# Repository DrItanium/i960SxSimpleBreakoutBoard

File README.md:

A very simple 4-layer breakout board for an i960Sx PLCC84 microprocessor.

The de-multiplexing hardware is separate in this design for ease of testing.

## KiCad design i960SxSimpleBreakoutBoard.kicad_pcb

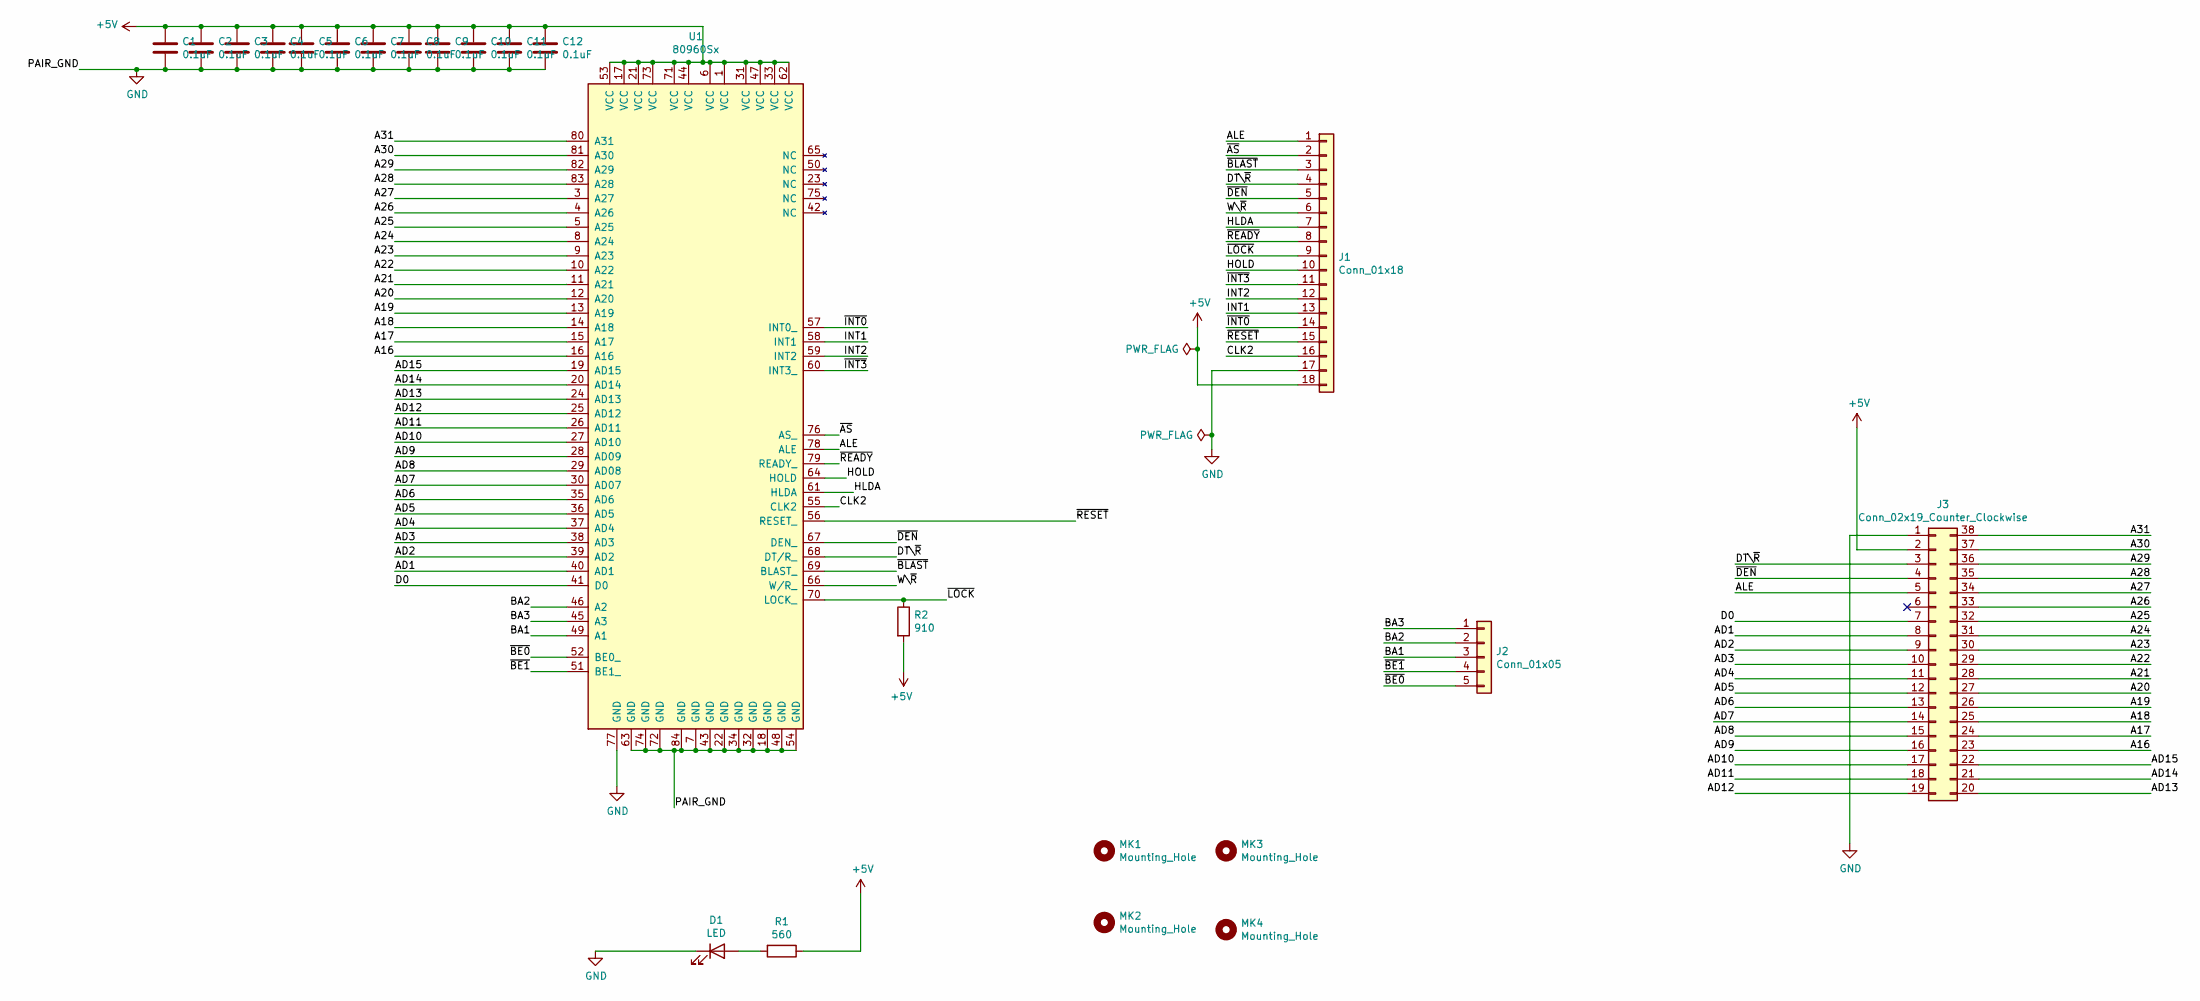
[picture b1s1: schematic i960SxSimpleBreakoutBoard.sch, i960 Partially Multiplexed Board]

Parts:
C1, C2, C3, C4, C5, C6, C7, C8, C9, C10, C11, C12: 0.1uF; C_0805_2012Metric_Pad1.15x1.40mm_HandSolder
D1: LED; LED_D5.0mm
J1: Conn_01x18; PinHeader_1x18_P2.54mm_Vertical
J2: Conn_01x05; PinHeader_1x05_P2.54mm_Vertical
J3: Conn_02x19_Counter_Clockwise; PinHeader_2x19_P2.54mm_Vertical
MK1, MK2, MK3, MK4: Mounting_Hole; MountingHole_3.2mm_M3
R1: 560; R_0805_2012Metric_Pad1.15x1.40mm_HandSolder
R2: 910; R_0805_2012Metric_Pad1.15x1.40mm_HandSolder
U1: 80960Sx; PLCC-84_THT-Socket

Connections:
+5V: C1.1, C2.1, C3.1, C4.1, C5.1, C6.1, C7.1, C8.1, C9.1, C10.1, C11.1, C12.1, J1.18, J3.2, R1.1, R2.2, U1.1 (VCC), U1.6 (VCC), U1.17 (VCC), U1.21 (VCC), U1.31 (VCC), U1.33 (VCC), U1.44 (VCC), U1.47 (VCC), U1.53 (VCC), U1.62 (VCC), U1.71 (VCC), U1.73 (VCC)
/A16: J3.23, U1.16 (A16)
/A17: J3.24, U1.15 (A17)
/A18: J3.25, U1.14 (A18)
/A19: J3.26, U1.13 (A19)
/A20: J3.27, U1.12 (A20)
/A21: J3.28, U1.11 (A21)
/A22: J3.29, U1.10 (A22)
/A23: J3.30, U1.9 (A23)
/A24: J3.31, U1.8 (A24)
/A25: J3.32, U1.5 (A25)
/A26: J3.33, U1.4 (A26)
/A27: J3.34, U1.3 (A27)
/A28: J3.35, U1.83 (A28)
/A29: J3.36, U1.82 (A29)
/A30: J3.37, U1.81 (A30)
/A31: J3.38, U1.80 (A31)
/AD1: J3.8, U1.40 (AD1)
/AD2: J3.9, U1.39 (AD2)
/AD3: J3.10, U1.38 (AD3)
/AD4: J3.11, U1.37 (AD4)
/AD5: J3.12, U1.36 (AD5)
/AD6: J3.13, U1.35 (AD6)
/AD7: J3.14, U1.30 (AD07)
/AD8: J3.15, U1.29 (AD08)
/AD9: J3.16, U1.28 (AD09)
/AD10: J3.17, U1.27 (AD10)
/AD11: J3.18, U1.26 (AD11)
/AD12: J3.19, U1.25 (AD12)
/AD13: J3.20, U1.24 (AD13)
/AD14: J3.21, U1.20 (AD14)
/AD15: J3.22, U1.19 (AD15)
/ALE: J1.1, J3.5, U1.78 (ALE)
/BA1: J2.3, U1.49 (A1)
/BA2: J2.2, U1.46 (A2)
/BA3: J2.1, U1.45 (A3)
/CLK2: J1.16, U1.55 (CLK2)
/D0: J3.7, U1.41 (D0)
/DT\~R: J1.4, J3.3, U1.68 (DT/R_)
/HLDA: J1.7, U1.61 (HLDA)
/HOLD: J1.10, U1.64 (HOLD)
/INT1: J1.13, U1.58 (INT1)
/INT2: J1.12, U1.59 (INT2)
/W\~R: J1.6, U1.66 (W/R_)
/~AS: J1.2, U1.76 (AS_)
/~BE0: J2.5, U1.52 (BE0_)
/~BE1: J2.4, U1.51 (BE1_)
/~BLAST: J1.3, U1.69 (BLAST_)
/~DEN: J1.5, J3.4, U1.67 (DEN_)
/~INT0: J1.14, U1.57 (INT0_)
/~INT3: J1.11, U1.60 (INT3_)
/~LOCK: J1.9, R2.1, U1.70 (LOCK_)
/~READY: J1.8, U1.79 (READY_)
/~RESET: J1.15, U1.56 (RESET_)
GND: C1.2, C2.2, C3.2, C4.2, C5.2, C6.2, C7.2, C8.2, C9.2, C10.2, C11.2, C12.2, D1.1 (K), J1.17, J3.1, U1.7 (GND), U1.18 (GND), U1.22 (GND), U1.32 (GND), U1.34 (GND), U1.43 (GND), U1.48 (GND), U1.54 (GND), U1.63 (GND), U1.72 (GND), U1.74 (GND), U1.77 (GND), U1.84 (GND)
unnamed: D1.2 (A), R1.2

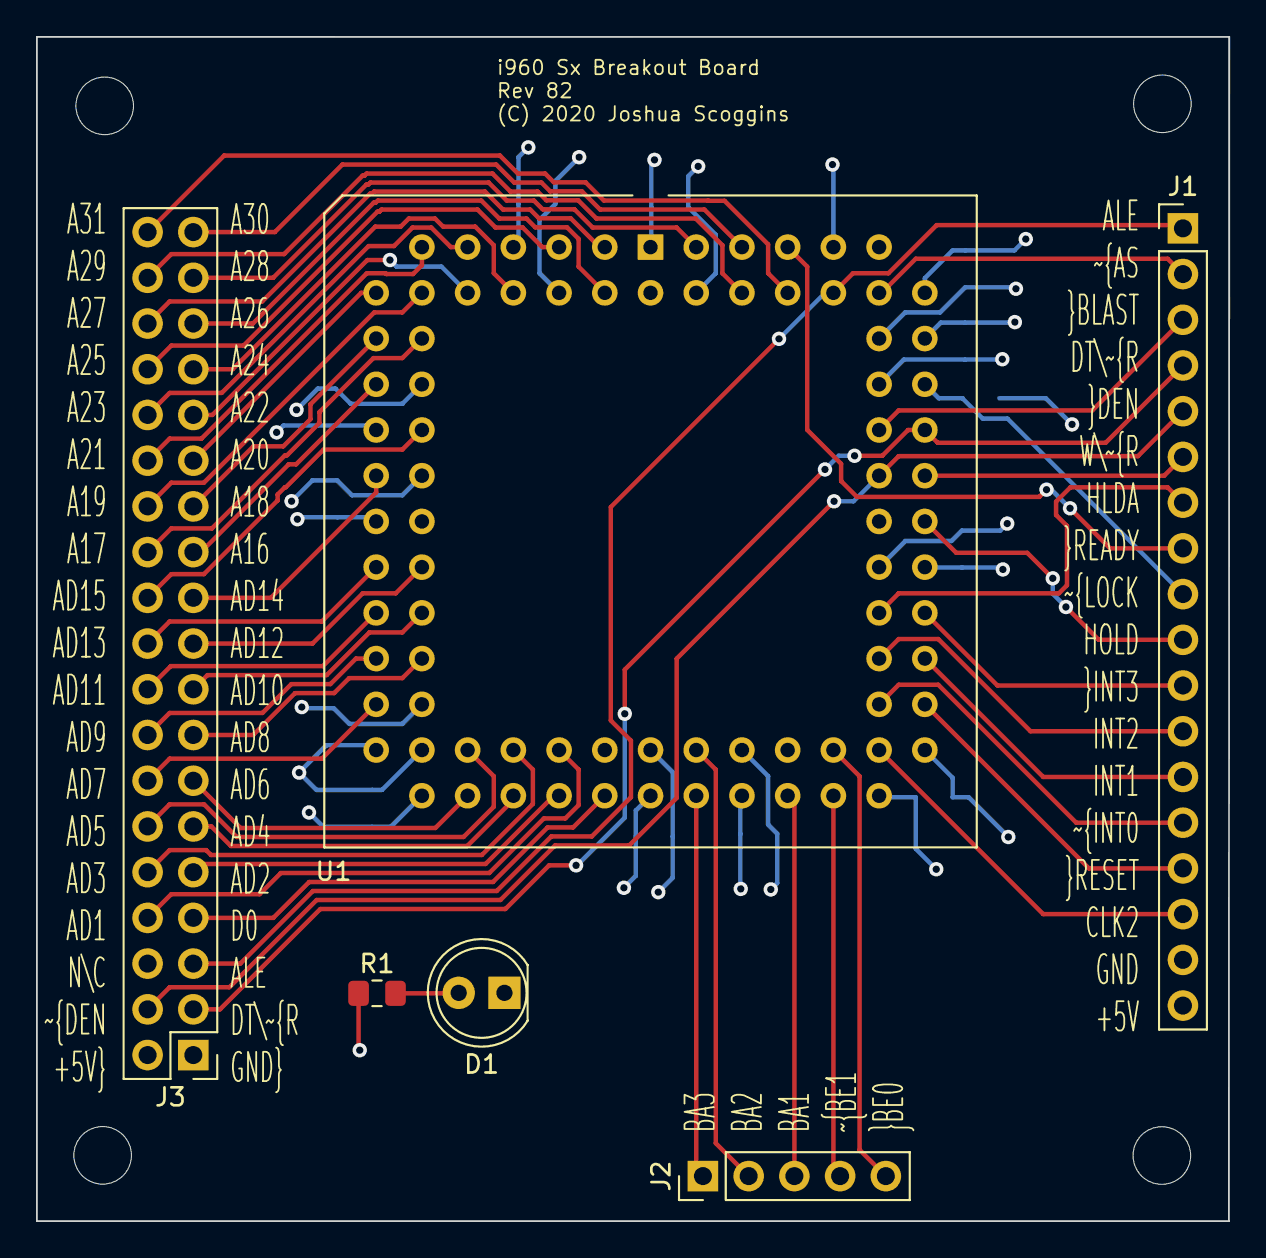
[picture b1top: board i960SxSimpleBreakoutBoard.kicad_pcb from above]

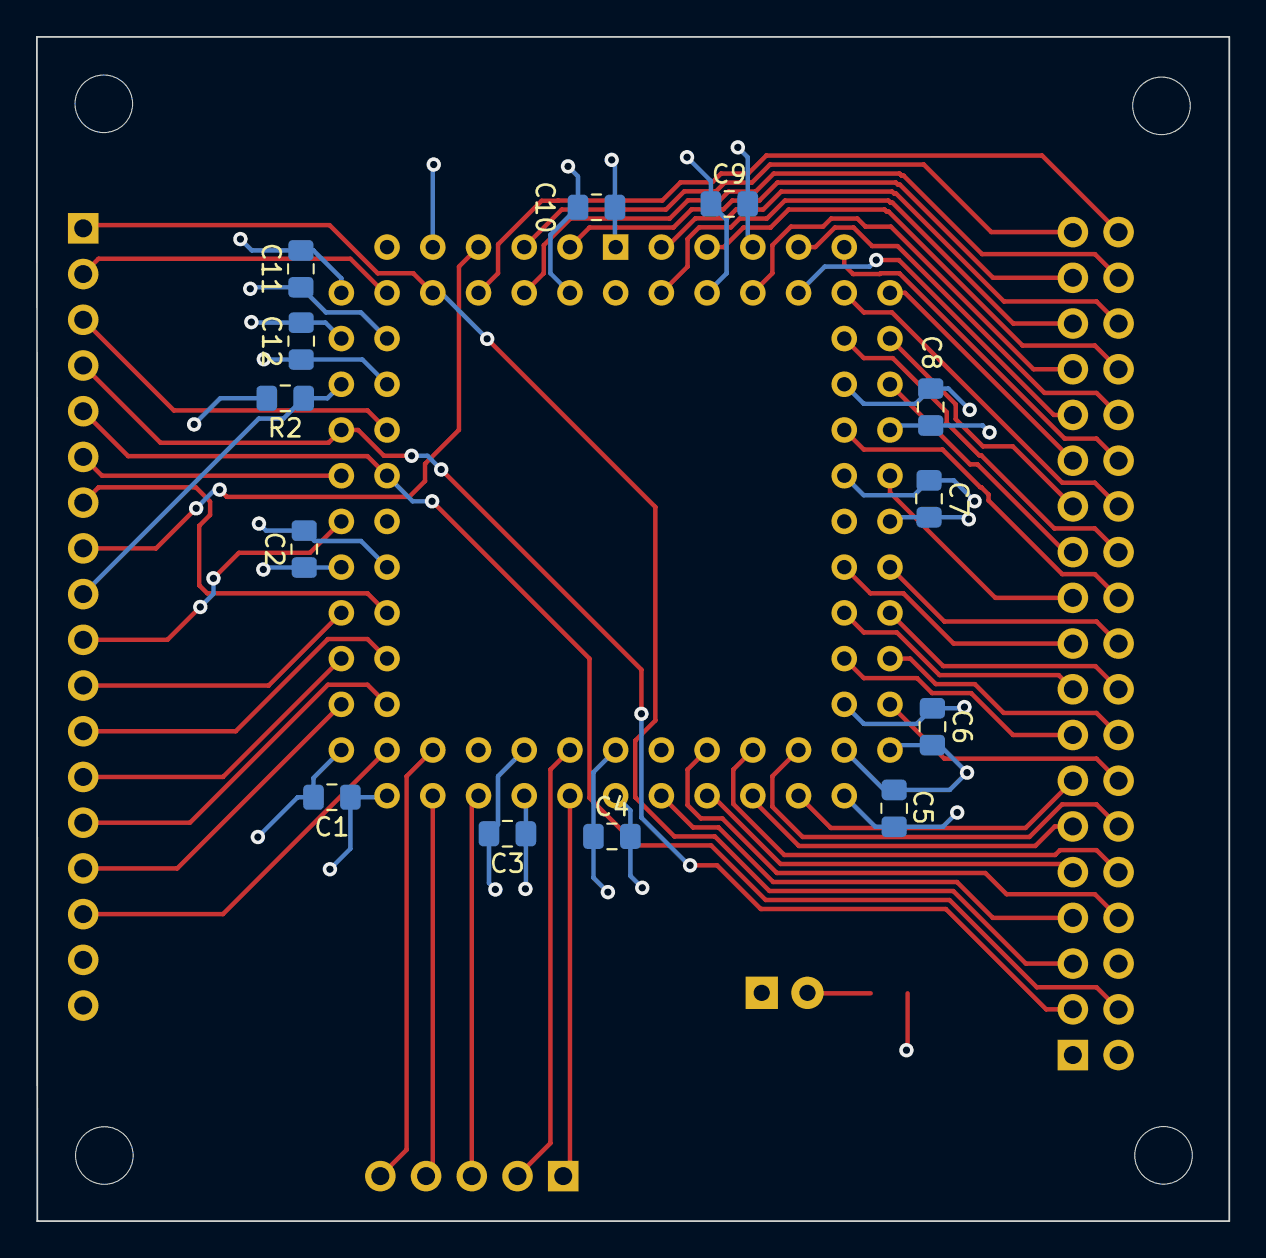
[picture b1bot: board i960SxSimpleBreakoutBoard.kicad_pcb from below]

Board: 4 copper layers, 66.2 x 65.8 mm, 23 parts (13 on the bottom side), 56 nets.

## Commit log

2020-11-21 Commit the files themselves
    This is the rev1 design that I'm currently using
2020-11-21 Start to move the demux hardware onto the breakout board
    Right now it is a separate module and is very annoying to wireup
2020-11-21 Eliminate the second set of multiplexed lines all together
2020-11-21 Consolidate control lines into fewer headers
    Address lines now have a single 01x32 header
2020-11-21 Add the data line breakout
    No sanity check errors :)
2020-11-21 Fix a typo
2020-11-21 Finish part selection
    We shall see if the board gets too large from this change or not
2020-11-21 Condense the pin headers further
2020-11-21 Proper part selection
2020-11-21 Widen the board to make routing easier
2020-11-21 Use single row headers in all cases now
2020-11-21 Modify pinout of control signals to make routing of traces easier
2020-11-21 Breakout getting more complex, need to switch to 40 pin cables
2020-11-22 Layout complete, no rpi cable at this time
    Too many lines, to put through a single cable
2020-11-22 Get rid of the mounting holes and put multiplexed lines on a single edge
2020-11-22 Address lines grouped together again
2020-11-22 Finish the initial rev 2 design
2020-11-22 sync
2020-11-23 go with a single 1 row connector for the right side of the design
2020-11-23 Shrunk the size of the final pcb
2020-11-23 Shave off some dimensions

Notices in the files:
i960SxSimpleBreakoutBoard.kicad_pcb:
(C) 2020 Joshua Scoggins
